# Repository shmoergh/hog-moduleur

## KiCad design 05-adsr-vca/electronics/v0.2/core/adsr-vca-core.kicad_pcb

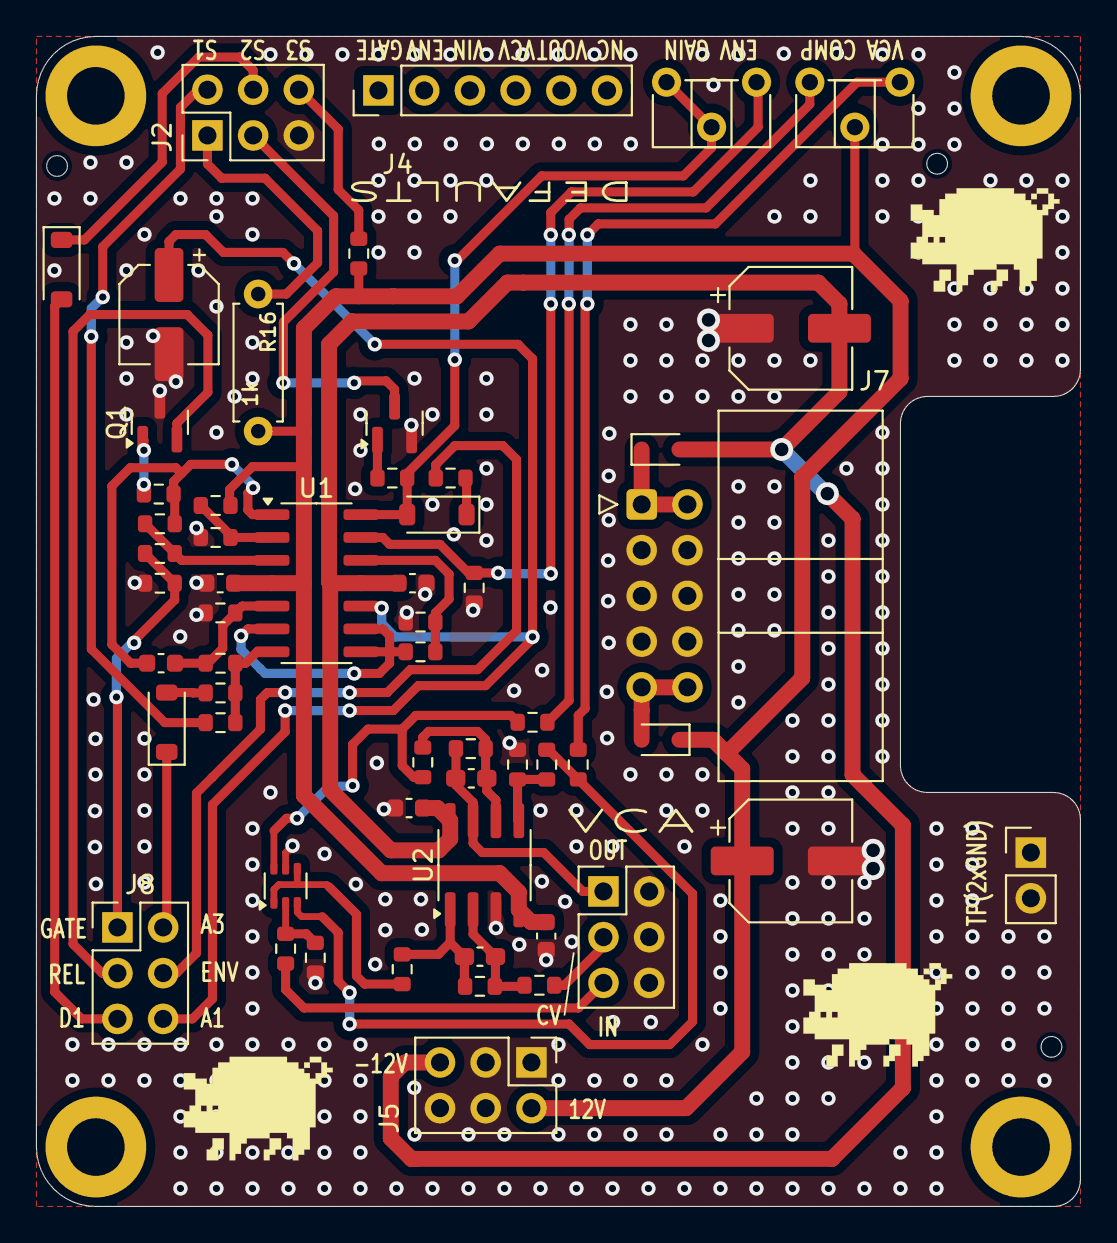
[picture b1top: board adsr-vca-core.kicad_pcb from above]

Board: 2 copper layers, 58.0 x 65.0 mm, 61 parts (0 on the bottom side), 42 nets.

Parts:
C1, C2, C5, C6: 100n; C_0603_1608Metric
C3: 10n; C_0603_1608Metric
C4: 10u; CP_Elec_5x5.4
C7, C8: 47p; C_0603_1608Metric_Pad1.08x0.95mm_HandSolder
C9, C10: 100u; CP_Elec_6.3x7.7
D1, D2, D3: 1N4148; D_SOD-123
D4, D5: 1N5817; D_SOD-323
H1, H2, H3, H4: MountingHole; MountingHole_3.2mm_M3_DIN965_Pad
J2, J3, J5, J8: Conn_02x03_Odd_Even; PinHeader_2x03_P2.54mm_Vertical
J4: Conn_01x06; PinHeader_1x06_P2.54mm_Vertical
J6: Conn_01x02; PinHeader_1x02_P2.54mm_Vertical
J7: Conn_02x05_Odd_Even; IDC-Header_2x05_P2.54mm_Horizontal
Q1: BC857; SOT-23
Q2: BC847; SOT-23
Q3: BC847BS; SOT-363_SC-70-6
R1: 22k; R_0603_1608Metric
R2, R4, R9, R17: 1k; R_0603_1608Metric
R3, R14, R15: 47k; R_0603_1608Metric
R5, R6, R7: 1M; R_0603_1608Metric
R8, R18, R22, R24: 100k; R_0603_1608Metric
R10, R12, R23, R25, R26: 10k; R_0603_1608Metric
R11: 4.7k; R_0603_1608Metric
R13: 15k; R_0603_1608Metric
R16: 1k; R_Axial_DIN0207_L6.3mm_D2.5mm_P7.62mm_Horizontal
R19: 200k; R_0603_1608Metric
R20: 220; R_0603_1608Metric
R21: 33k; R_0603_1608Metric
R27, R28: 470k; R_0603_1608Metric
RV_COMP1: 10k; Potentiometer_ACP_CA6-H2,5_Horizontal
RV_OUT_GAIN1: 100k; Potentiometer_ACP_CA6-H2,5_Horizontal
U1: LM324; SOIC-14_3.9x8.7mm_P1.27mm
U2: TL072; SOIC-8_3.9x4.9mm_P1.27mm

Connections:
+12V: C1.1, C5.1, C9.1, D4.1 (K), J5.2, R1.2, R11.1, R16.2, RV_COMP1.2, U1.4 (V+), U2.4 (V-)
-12V: C2.2, C6.2, C10.2, D5.2 (A), J5.5, U1.11 (V-), U2.8 (V+)
A1_D3_R3: C4.1, J8.6, U1.10 (+)
ATTACK_3: D1.1 (K), J8.2
DECAY_1: D2.2 (A), J8.5
ENV_OUT: J8.4, R17.1
GATE: J8.1, R3.2, R4.2
GND: C1.2, C2.1, C4.2, C5.2, C6.1, C9.2, C10.1, J2.5, J3.2, J3.4, J3.6, J5.1, J5.3, J5.4, J5.6, J6.1, J6.2, J7.3, J7.4, J7.5, J7.6, J7.7, J7.8, Q1.3 (C), Q2.2 (E), Q3.5 (B2), R2.1, R3.1, R6.1, R13.1, R14.1, R20.1, R27.1, U2.3 (+)
LED_A: J2.1, R16.1
LED_K: J2.3, Q2.3 (C)
unnamed: C3.1, R5.1, R8.2, U1.1
unnamed: C7.2, R21.2, R23.1, U2.1
unnamed: D1.2 (A), R9.1
unnamed: D3.2 (A), R15.2, RV_OUT_GAIN1.2, RV_OUT_GAIN1.3, U1.14
unnamed: D3.1 (K), R17.2
unnamed: D4.2 (A), J7.9, J7.10
unnamed: D5.1 (K), J7.1, J7.2
unnamed: Q1.1 (B), R8.1
unnamed: Q2.1 (B), R15.1
unnamed: Q3.2 (B1), R18.2, R20.2
unnamed: Q3.6 (C1), R22.1, R25.1
unnamed: Q3.1 (E1), Q3.4 (E2), R23.2
unnamed: Q3.3 (C2), R24.1, R26.1
unnamed: R7.1, R9.2, R10.2, U1.7
unnamed: R22.2, RV_COMP1.3
unnamed: R24.2, RV_COMP1.1
unnamed: R4.1, R5.2, U1.3 (+)
unnamed: R1.1, R2.2, U1.2 (-)
unnamed: C3.2, R6.2, R7.2, U1.5 (+)
unnamed: R12.2, U1.6 (-), U1.8, U1.9 (-)
unnamed: R12.1, R13.2, U1.12 (+)
unnamed: R14.2, RV_OUT_GAIN1.1, U1.13 (-)
unnamed: C7.1, R19.2, R21.1, U2.2 (-)
unnamed: R26.2, R27.2, U2.5 (+)
unnamed: C8.1, R25.2, R28.1, U2.6 (-)
RELEASE_1: J8.3, Q1.2 (E)
SUSTAIN_1: J2.2, R10.1
SUSTAIN_2: D2.1 (K), J2.4
SUSTAIN_3: J2.6, R11.2
VCA_CV: J3.3, R19.1
VCA_IN: J3.5, R18.1
VCA_OUT: C8.2, J3.1, R28.2, U2.7

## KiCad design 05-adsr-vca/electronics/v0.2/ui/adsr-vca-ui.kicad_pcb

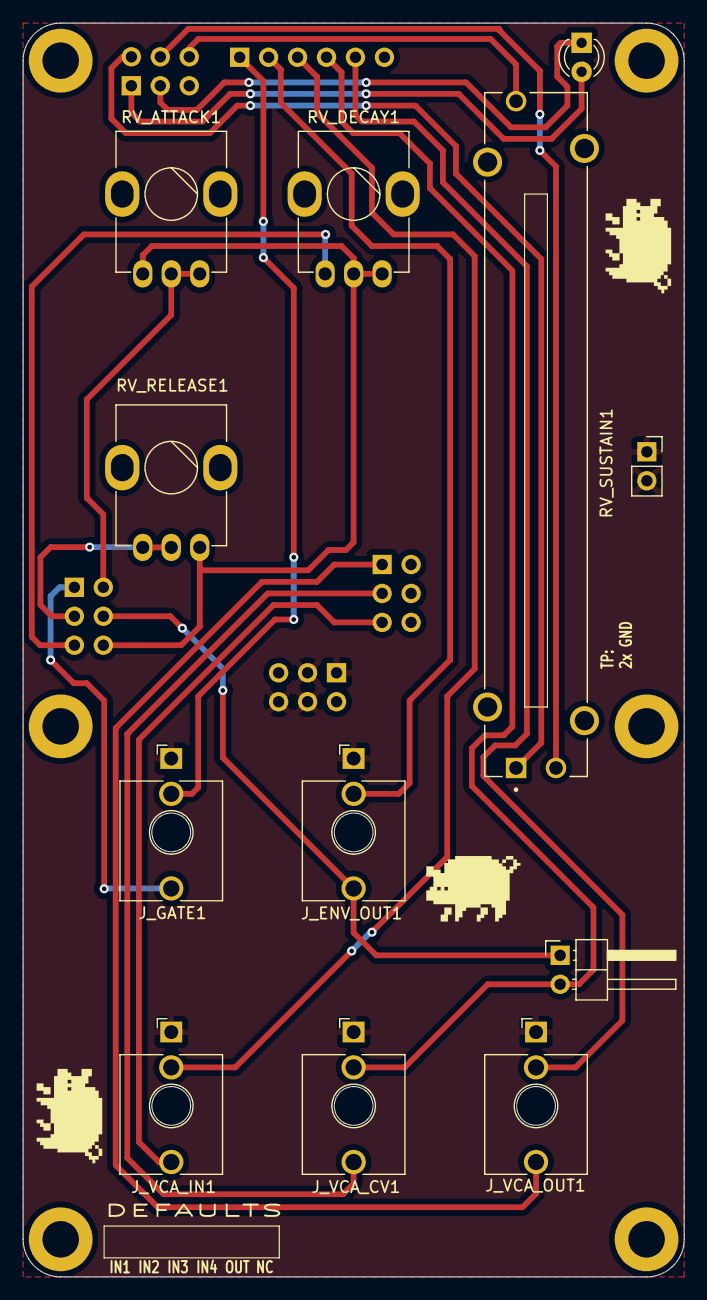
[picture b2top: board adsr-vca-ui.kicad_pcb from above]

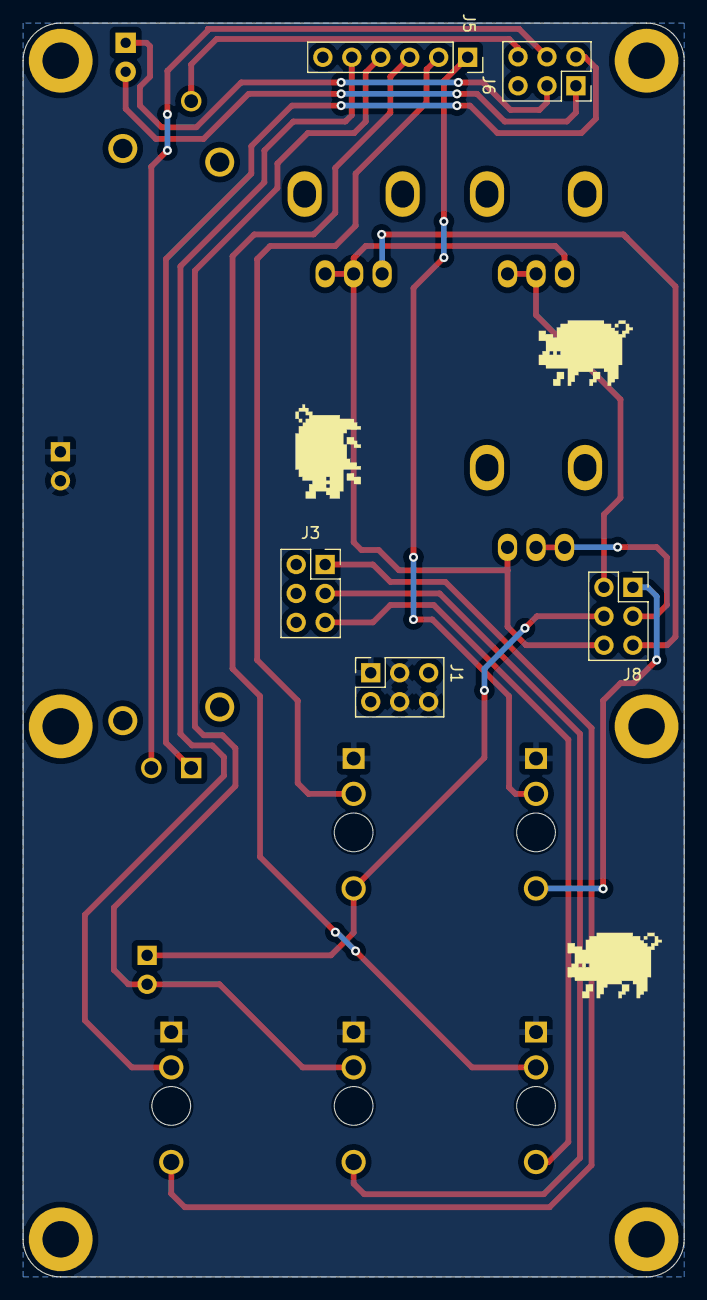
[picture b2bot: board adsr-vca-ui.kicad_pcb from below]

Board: 2 copper layers, 58.0 x 110.0 mm, 23 parts (5 on the bottom side), 20 nets.

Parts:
D1: D; LED_D3.0mm
H1, H2, H3, H4, H5, H6: MountingHole; MountingHole_3.2mm_M3_DIN965_Pad
J1, J3, J6, J8: Conn_02x03_Odd_Even; PinSocket_2x03_P2.54mm_Vertical
J4: Conn_01x02; PinSocket_1x02_P2.54mm_Vertical
J5: Conn_01x06; PinSocket_1x06_P2.54mm_Vertical
JP_DEFAULT_ENV_TO_VCA1: Jumper_2_Open; PinHeader_1x02_P2.54mm_Horizontal
J_ENV_OUT1: PJ398SM; Jack_3.5mm_QingPu_WQP-PJ398SM_Vertical_CircularHoles
J_GATE1: PJ398SM; Jack_3.5mm_QingPu_WQP-PJ398SM_Vertical_CircularHoles
J_VCA_CV1: PJ398SM; Jack_3.5mm_QingPu_WQP-PJ398SM_Vertical_CircularHoles
J_VCA_IN1: PJ398SM; Jack_3.5mm_QingPu_WQP-PJ398SM_Vertical_CircularHoles
J_VCA_OUT1: PJ398SM; Jack_3.5mm_QingPu_WQP-PJ398SM_Vertical_CircularHoles
RV_ATTACK1: A500k; Potentiometer_Bourns_Single-PTV09A
RV_DECAY1: A500k; Potentiometer_Bourns_Single-PTV09A
RV_RELEASE1: A500k; Potentiometer_Bourns_Single-PTV09A
RV_SUSTAIN1: 10k; TRIM_PTA4543-2015DPB103

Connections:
A1_D3_R3: J8.6, RV_ATTACK1.1, RV_DECAY1.2, RV_DECAY1.3, RV_RELEASE1.3
ATTACK_3: J8.2, RV_ATTACK1.2, RV_ATTACK1.3
DECAY_1: J8.5, RV_DECAY1.1
ENV_OUT: J8.4, JP_DEFAULT_ENV_TO_VCA1.1 (A), J_ENV_OUT1.T
ENV_OUT_DEFAULT: J5.2, J_ENV_OUT1.TN
GATE: J8.1, J_GATE1.T
GATE_DEFAULT: J5.1, J_GATE1.TN
GND: J1.1, J1.3, J1.4, J1.6, J4.1, J4.2, J_ENV_OUT1.S, J_GATE1.S, J_VCA_CV1.S, J_VCA_IN1.S, J_VCA_OUT1.S
LED_A: D1.2 (A), J6.1
LED_K: D1.1 (K), J6.3
RELEASE_1: J8.3, RV_RELEASE1.1, RV_RELEASE1.2
SUSTAIN_1: J6.2, RV_SUSTAIN1.1
SUSTAIN_2: J6.4, RV_SUSTAIN1.2
SUSTAIN_3: J6.6, RV_SUSTAIN1.3
VCA_CV: J3.3, J_VCA_CV1.T
VCA_CV_DEFAULT: J5.4, JP_DEFAULT_ENV_TO_VCA1.2 (B), J_VCA_CV1.TN
VCA_IN: J3.5, J_VCA_IN1.T
VCA_IN_DEFAULT: J5.3, J_VCA_IN1.TN
VCA_OUT: J3.1, J_VCA_OUT1.T
VCA_OUT_DEFAULT: J5.5, J_VCA_OUT1.TN

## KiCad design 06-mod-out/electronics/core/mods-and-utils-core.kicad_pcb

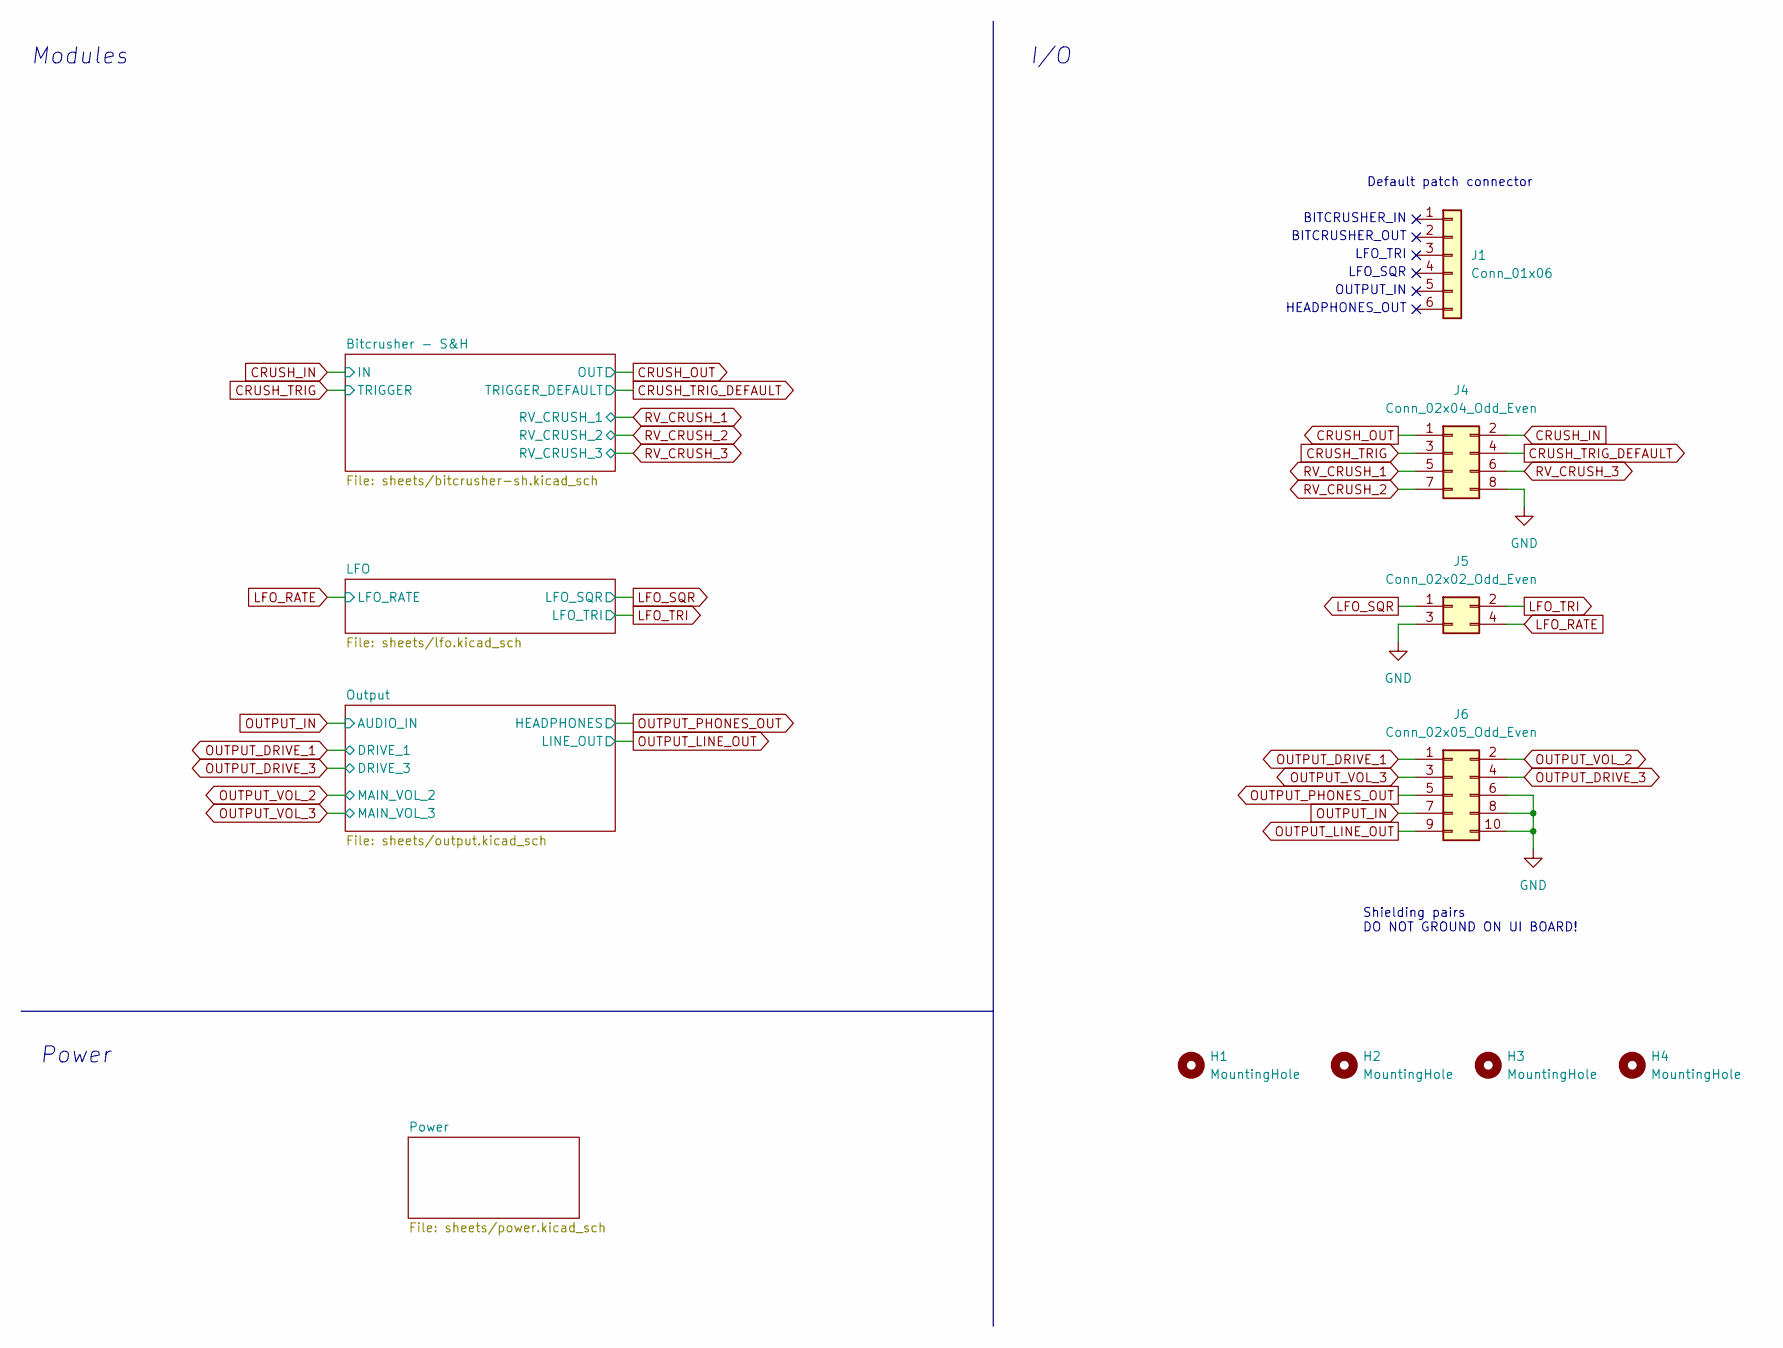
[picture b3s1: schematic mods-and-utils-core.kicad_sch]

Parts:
H1, H2, H3, H4: MountingHole; MountingHole_3.2mm_M3_DIN965_Pad
J1: Conn_01x06; PinHeader_1x06_P2.54mm_Vertical
J4: Conn_02x04_Odd_Even; PinHeader_2x04_P2.54mm_Vertical
J5: Conn_02x02_Odd_Even; PinHeader_2x02_P2.54mm_Vertical
J6: Conn_02x05_Odd_Even; PinHeader_2x05_P2.54mm_Vertical

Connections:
CRUSH_IN: J4.2; also elsewhere on the board
CRUSH_OUT: J4.1; also elsewhere on the board
CRUSH_TRIG: J4.3; also elsewhere on the board
CRUSH_TRIG_DEFAULT: J4.4; also elsewhere on the board
GND: J4.8, J5.3, J6.6, J6.8, J6.10; also elsewhere on the board
LFO_RATE: J5.4; also elsewhere on the board
LFO_SQR: J5.1; also elsewhere on the board
LFO_TRI: J5.2; also elsewhere on the board
OUTPUT_DRIVE_1: J6.1; also elsewhere on the board
OUTPUT_DRIVE_3: J6.4; also elsewhere on the board
OUTPUT_IN: J6.7; also elsewhere on the board
OUTPUT_LINE_OUT: J6.9; also elsewhere on the board
OUTPUT_PHONES_OUT: J6.5; also elsewhere on the board
OUTPUT_VOL_2: J6.2; also elsewhere on the board
OUTPUT_VOL_3: J6.3; also elsewhere on the board
RV_CRUSH_1: J4.5; also elsewhere on the board
RV_CRUSH_2: J4.7; also elsewhere on the board
RV_CRUSH_3: J4.6; also elsewhere on the board

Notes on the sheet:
Power
LFO_TRI
Default patch connector
HEADPHONES_OUT
BITCRUSHER_IN
Shielding pairs DO NOT GROUND ON UI BOARD!
OUTPUT_IN
Modules
BITCRUSHER_OUT
I/O
LFO_SQR

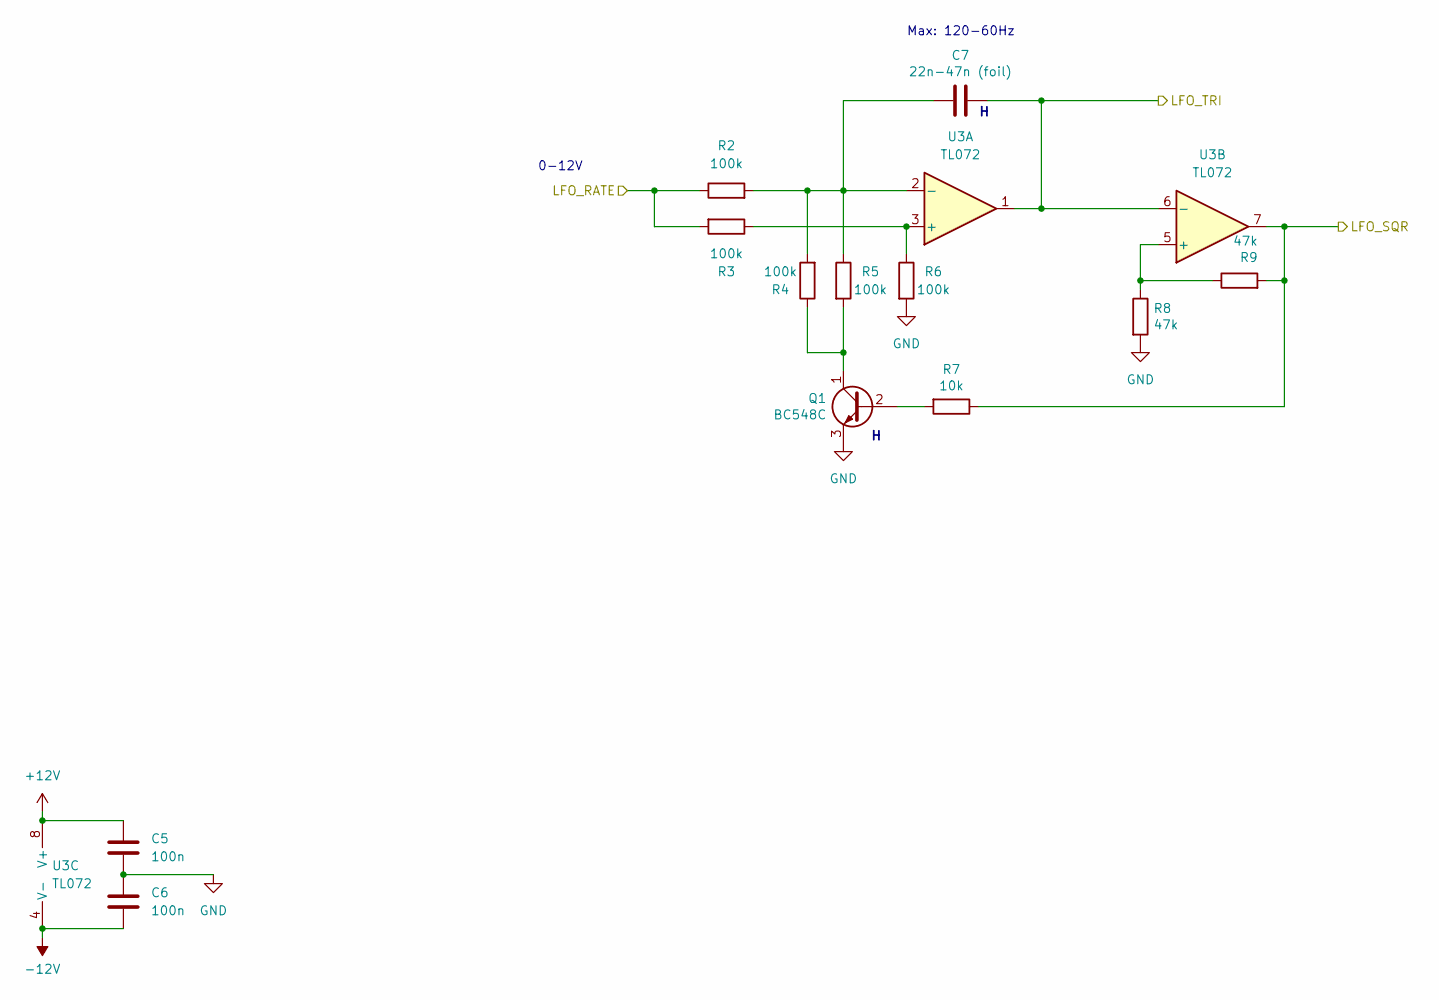
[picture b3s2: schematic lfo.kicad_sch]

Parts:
C5, C6: 100n; C_0603_1608Metric; LCSC C14663
C7: 22n-47n (foil); C_Rect_L7.0mm_W2.5mm_P5.00mm; Part No. 80-R82EC1330AA50K
Q1: BC548C; TO-92L_Inline_Wide; Part No. 637-BC548C
R2, R3, R4, R5, R6: 100k; R_0603_1608Metric; LCSC C25803
R7: 10k; R_0603_1608Metric; LCSC C25804
R8, R9: 47k; R_0603_1608Metric; LCSC C25819
U3: TL072; SOIC-8_3.9x4.9mm_P1.27mm; LCSC C6961

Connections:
+12V: C5.1, U3.8 (V+); also elsewhere on the board
-12V: C6.2, U3.4 (V-); also elsewhere on the board
GND: C5.2, C6.1, Q1.3 (E), R6.2, R8.2; also elsewhere on the board
LFO_RATE: R2.1, R3.2; also elsewhere on the board
LFO_TRI: C7.1, U3.1, U3.6 (-); also elsewhere on the board
unnamed 19: Q1.2 (B), R7.2; also elsewhere on the board
unnamed 20: Q1.1 (C), R4.1, R5.2; also elsewhere on the board
unnamed 23: R7.1, R9.2, U3.7; also elsewhere on the board
unnamed: R3.1, R6.1, U3.3 (+)
unnamed: C7.2, R2.2, R4.2, R5.1, U3.2 (-)
unnamed: R8.1, R9.1, U3.5 (+)

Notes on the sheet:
Max: 120-60Hz
0-12V

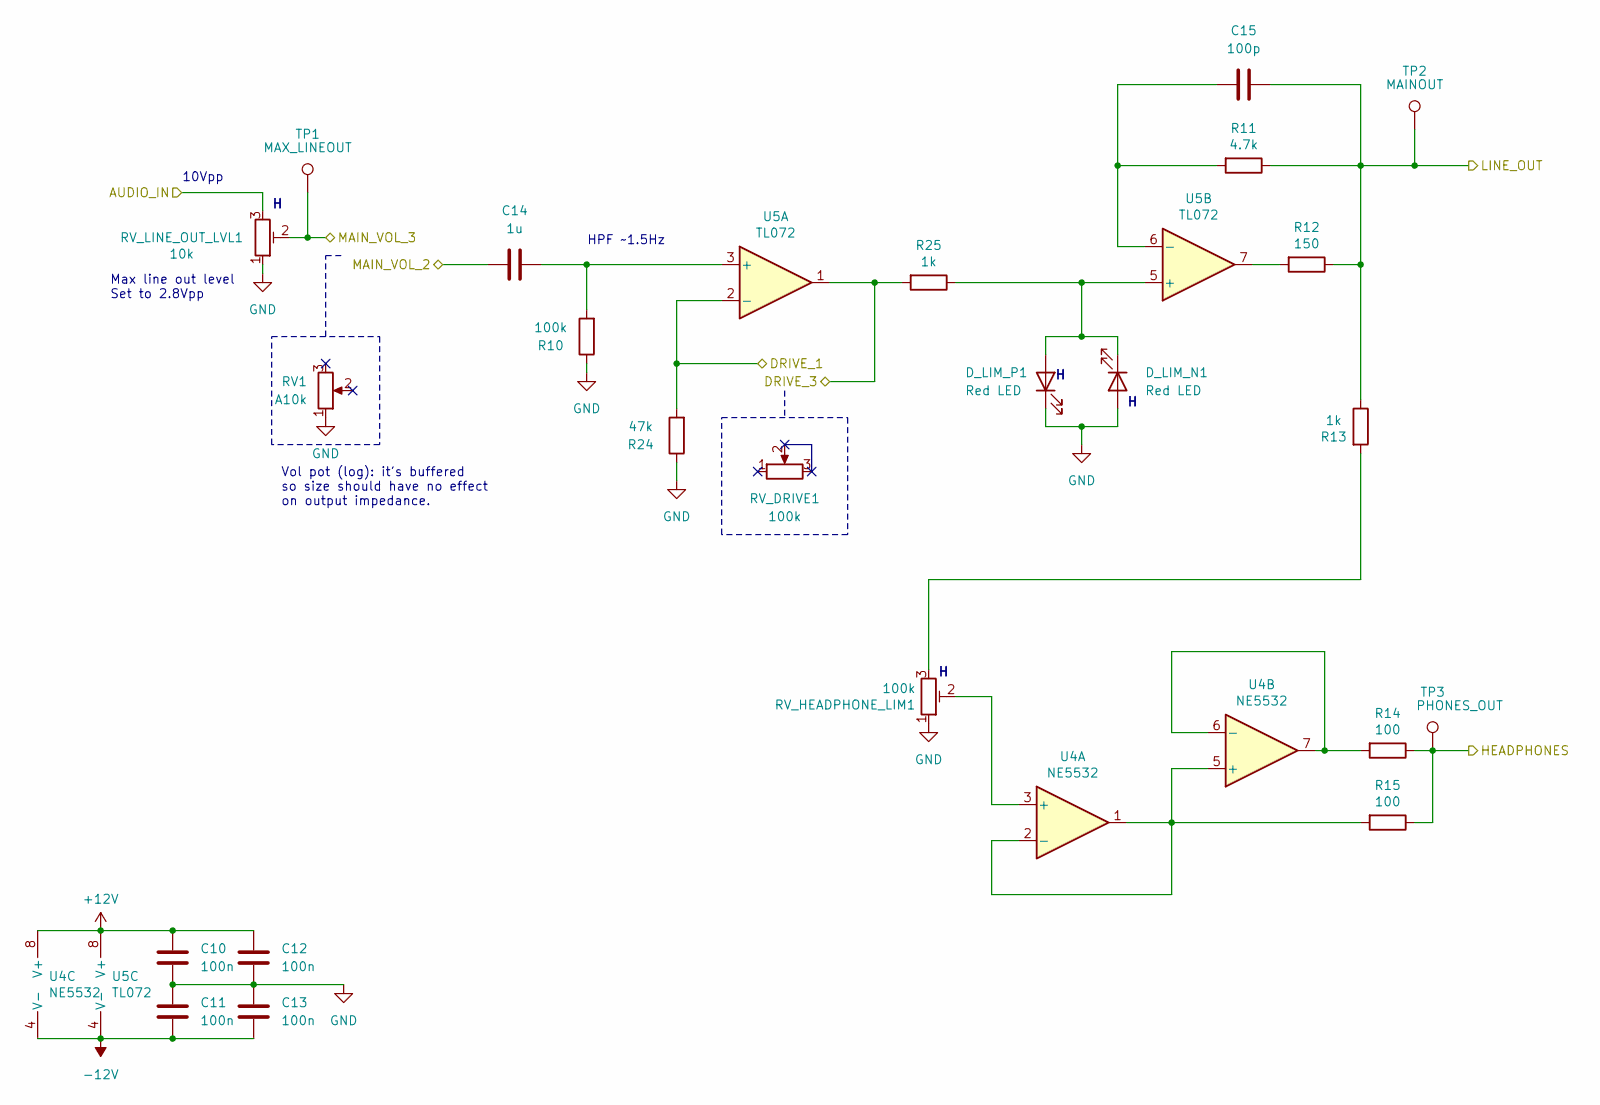
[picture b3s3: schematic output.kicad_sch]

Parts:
C10, C11, C12, C13: 100n; C_0603_1608Metric; LCSC C14663
C14: 1u; C_0603_1608Metric_Pad1.08x0.95mm_HandSolder; LCSC C15849
C15: 100p; C_0603_1608Metric; LCSC C14858
D_LIM_N1: Red LED; LED_D5.0mm
D_LIM_P1: Red LED; LED_D5.0mm
R10: 100k; R_0603_1608Metric_Pad0.98x0.95mm_HandSolder; LCSC C25803
R11: 4.7k; R_0603_1608Metric; LCSC C23162
R12: 150; R_0603_1608Metric; LCSC C22808
R13, R25: 1k; R_0603_1608Metric; LCSC C21190
R14, R15: 100; R_0603_1608Metric; LCSC C22775
R24: 47k; R_0603_1608Metric_Pad0.98x0.95mm_HandSolder
RV1: A10k
RV_DRIVE1: 100k
RV_HEADPHONE_LIM1: 100k; Potentiometer_ACP_CA6-H2,5_Horizontal; Part No. 531-PT6KH104A1010PM
RV_LINE_OUT_LVL1: 10k; Potentiometer_ACP_CA6-H2,5_Horizontal; Part No. 531-PT6KH-10K
TP1: MAX_LINEOUT; TestPoint_THTPad_2.0x2.0mm_Drill1.0mm
TP2: MAINOUT; TestPoint_THTPad_2.0x2.0mm_Drill1.0mm
TP3: PHONES_OUT; TestPoint_THTPad_2.0x2.0mm_Drill1.0mm
U4: NE5532; SOIC-8_3.9x4.9mm_P1.27mm; LCSC C7426
U5: TL072; SOIC-8_3.9x4.9mm_P1.27mm; LCSC C6961

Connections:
+12V: C10.1, C12.1, U4.8 (V+), U5.8 (V+); also elsewhere on the board
-12V: C11.2, C13.2, U4.4 (V-), U5.4 (V-); also elsewhere on the board
GND: C10.2, C11.1, C12.2, C13.1, D_LIM_N1.2 (A), D_LIM_P1.1 (K), R10.1, R24.1, RV1.1, RV_HEADPHONE_LIM1.1, RV_LINE_OUT_LVL1.1; also elsewhere on the board
unnamed: D_LIM_N1.1 (K), D_LIM_P1.2 (A), R25.1, U5.5 (+)
unnamed: R12.2, U5.7
unnamed: R13.2, RV_HEADPHONE_LIM1.3
unnamed: RV_HEADPHONE_LIM1.2, U4.3 (+)
unnamed: R15.2, U4.1, U4.2 (-), U4.5 (+)
unnamed: R14.2, U4.6 (-), U4.7
unnamed: C14.2, R10.2, U5.3 (+)
unnamed: C15.1, R11.2, U5.6 (-)
OUTPUT_DRIVE_1: R24.2, U5.2 (-); also elsewhere on the board
OUTPUT_DRIVE_3: R25.2, U5.1; also elsewhere on the board
OUTPUT_IN: RV_LINE_OUT_LVL1.3; also elsewhere on the board
OUTPUT_LINE_OUT: C15.2, R11.1, R12.1, R13.1, TP2.1; also elsewhere on the board
OUTPUT_PHONES_OUT: R14.1, R15.1, TP3.1; also elsewhere on the board
OUTPUT_VOL_2: C14.1; also elsewhere on the board
OUTPUT_VOL_3: RV_LINE_OUT_LVL1.2, TP1.1; also elsewhere on the board

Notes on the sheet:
Vol pot (log): it's buffered so size should have no effect on output impedance.
HPF ~1.5Hz
Max line out level Set to 2.8Vpp
10Vpp

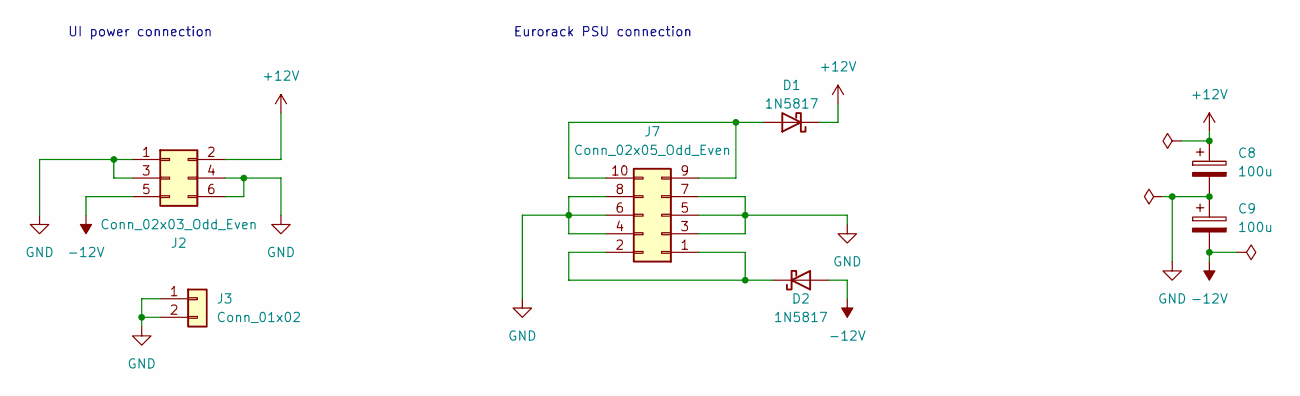
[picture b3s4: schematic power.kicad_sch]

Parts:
C8, C9: 100u; CP_Elec_6.3x7.7; LCSC C2836437
D1, D2: 1N5817; D_SOD-323; LCSC C5190152
J2: Conn_02x03_Odd_Even; PinHeader_2x03_P2.54mm_Vertical
J3: Conn_01x02; PinHeader_1x02_P2.54mm_Vertical
J7: Conn_02x05_Odd_Even; IDC-Header_2x05_P2.54mm_Horizontal

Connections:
+12V: C8.1, D1.1 (K), J2.2; also elsewhere on the board
-12V: C9.2, D2.2 (A), J2.5; also elsewhere on the board
GND: C8.2, C9.1, J2.1, J2.3, J2.4, J2.6, J3.1, J3.2, J7.3, J7.4, J7.5, J7.6, J7.7, J7.8; also elsewhere on the board
unnamed: D1.2 (A), J7.9, J7.10
unnamed: D2.1 (K), J7.1, J7.2

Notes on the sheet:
UI power connection
Eurorack PSU connection

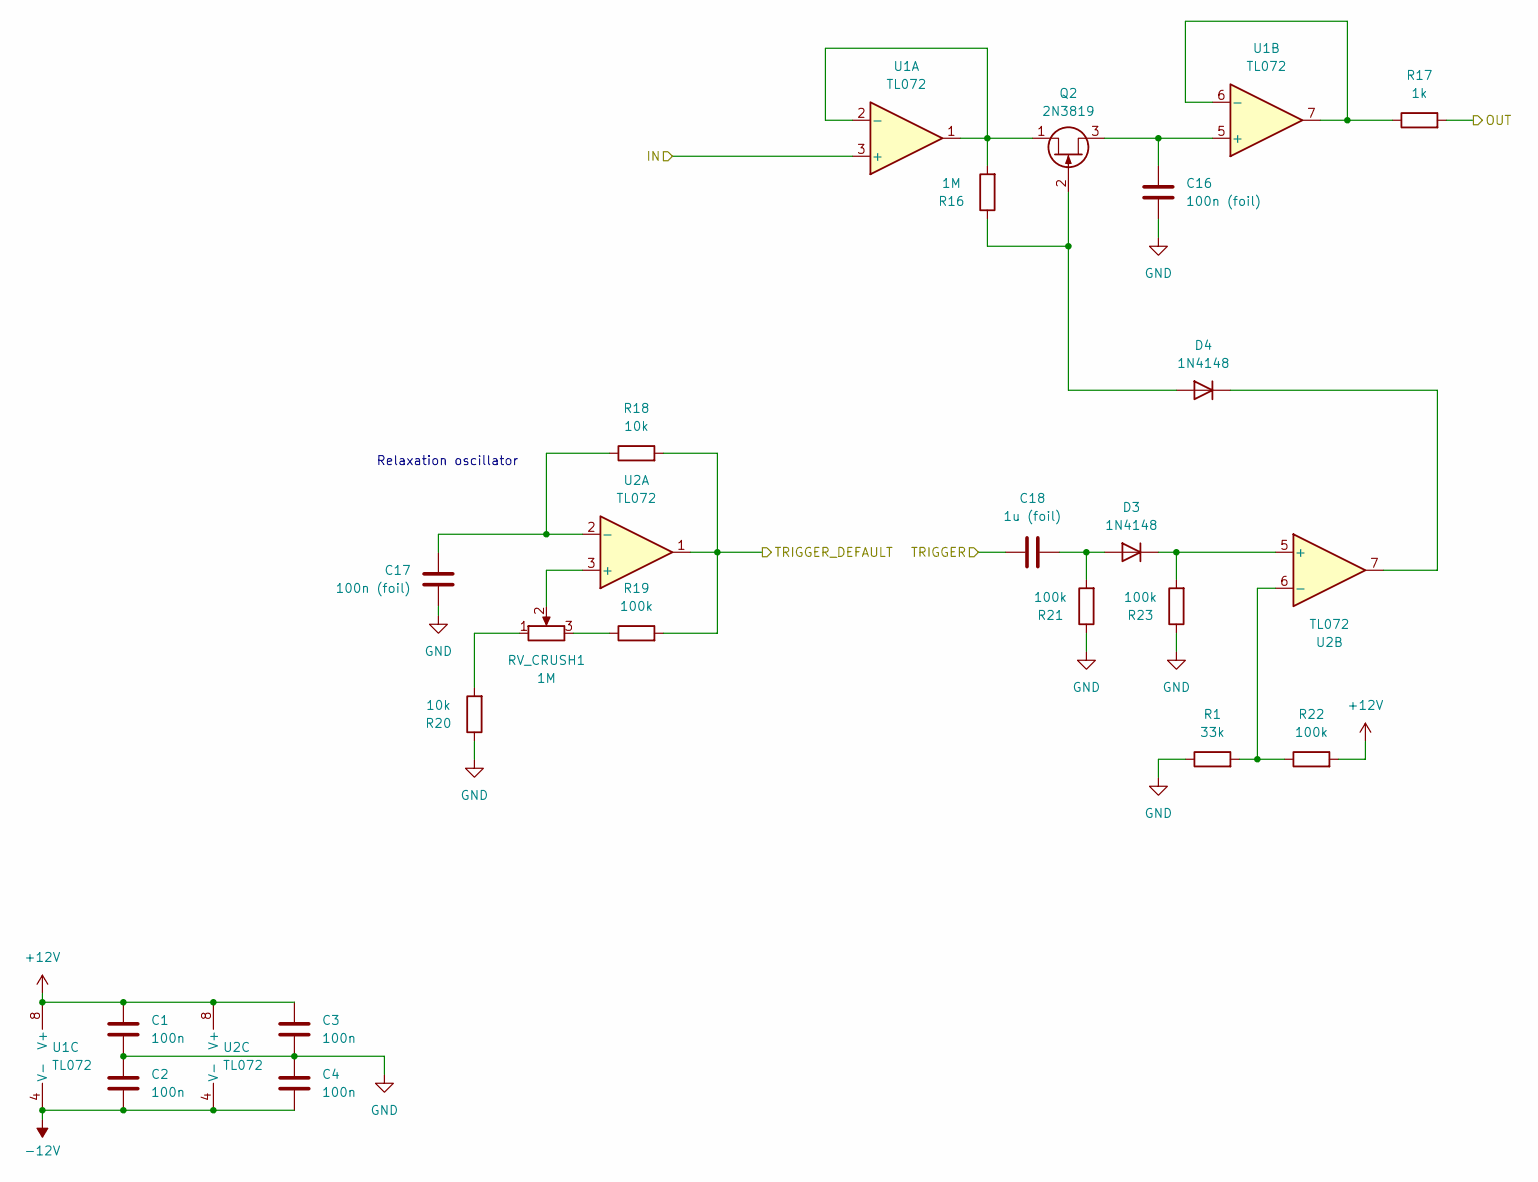
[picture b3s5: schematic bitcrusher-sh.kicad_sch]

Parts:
C1, C2, C3, C4: 100n; C_0603_1608Metric; LCSC C14663
C16, C17: 100n (foil); C_Rect_L7.2mm_W2.5mm_P5.00mm_FKS2_FKP2_MKS2_MKP2
C18: 1u (foil); C_Rect_L7.0mm_W4.5mm_P5.00mm
D3, D4: 1N4148; D_SOD-123; LCSC C81598
Q2: 2N3819; TO-92
R1: 33k; R_0603_1608Metric
R16: 1M; R_0603_1608Metric
R17: 1k; R_0603_1608Metric
R18, R20: 10k; R_0603_1608Metric
R19, R21, R22, R23: 100k; R_0603_1608Metric
RV_CRUSH1: 1M
U1, U2: TL072; SOIC-8_3.9x4.9mm_P1.27mm; LCSC C6961

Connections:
+12V: C1.1, C3.1, R22.2, U1.8 (V+), U2.8 (V+); also elsewhere on the board
-12V: C2.2, C4.2, U1.4 (V-), U2.4 (V-); also elsewhere on the board
CRUSH_IN: U1.3 (+); also elsewhere on the board
CRUSH_OUT: R17.2; also elsewhere on the board
CRUSH_TRIG: C18.1; also elsewhere on the board
CRUSH_TRIG_DEFAULT: R18.2, R19.2, U2.1; also elsewhere on the board
GND: C1.2, C2.1, C3.2, C4.1, C16.2, C17.2, R1.1, R20.1, R21.1, R23.1; also elsewhere on the board
unnamed: C18.2, D3.2 (A), R21.2
unnamed: D3.1 (K), R23.2, U2.5 (+)
unnamed: D4.2 (A), Q2.2 (G), R16.1
unnamed: D4.1 (K), U2.7
unnamed: Q2.1 (D), R16.2, U1.1, U1.2 (-)
unnamed: C16.1, Q2.3 (S), U1.5 (+)
unnamed: R17.1, U1.6 (-), U1.7
unnamed: C17.1, R18.1, U2.2 (-)
unnamed: R1.2, R22.1, U2.6 (-)
RV_CRUSH_1: R20.2, RV_CRUSH1.1; also elsewhere on the board
RV_CRUSH_2: RV_CRUSH1.2, U2.3 (+); also elsewhere on the board
RV_CRUSH_3: R19.1, RV_CRUSH1.3; also elsewhere on the board

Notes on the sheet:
Relaxation oscillator

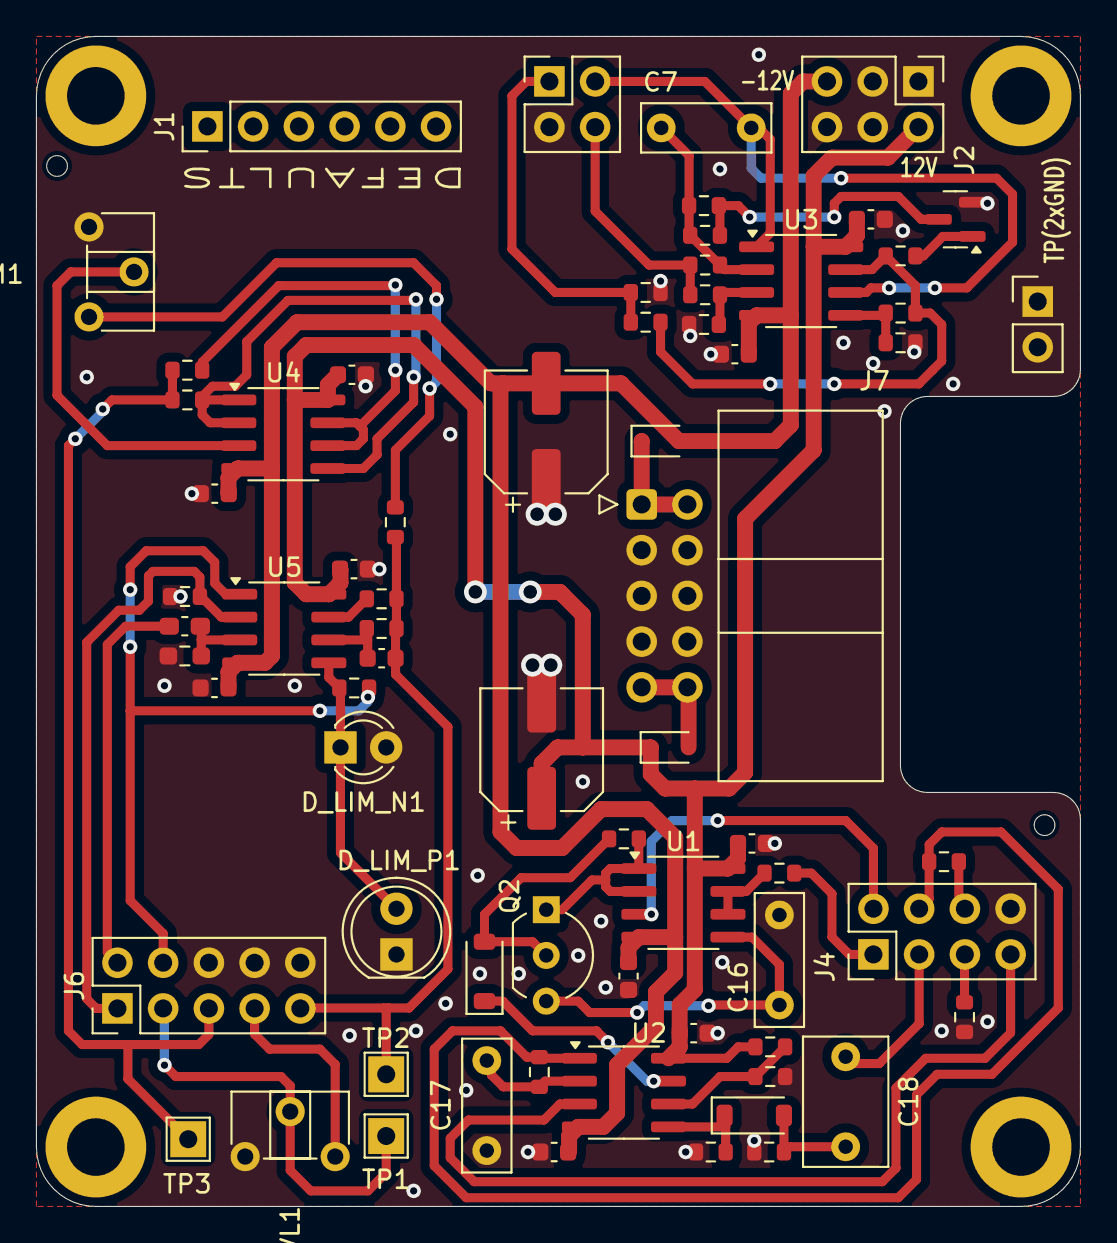
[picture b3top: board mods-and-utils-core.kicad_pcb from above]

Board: 2 copper layers, 58.0 x 65.0 mm, 74 parts (0 on the bottom side), 45 nets.

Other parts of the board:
Q4: BC848; SOT-23
R26: 12k; R_0603_1608Metric
R27: 47k; R_0603_1608Metric

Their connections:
GND: Q4.2 (E), R27.2; also elsewhere on the board
LFO_SQR: R26.2, R27.1; also elsewhere on the board
unnamed 19: Q4.1 (B); also elsewhere on the board
unnamed 20: Q4.3 (C); also elsewhere on the board
unnamed 23: R26.1; also elsewhere on the board
